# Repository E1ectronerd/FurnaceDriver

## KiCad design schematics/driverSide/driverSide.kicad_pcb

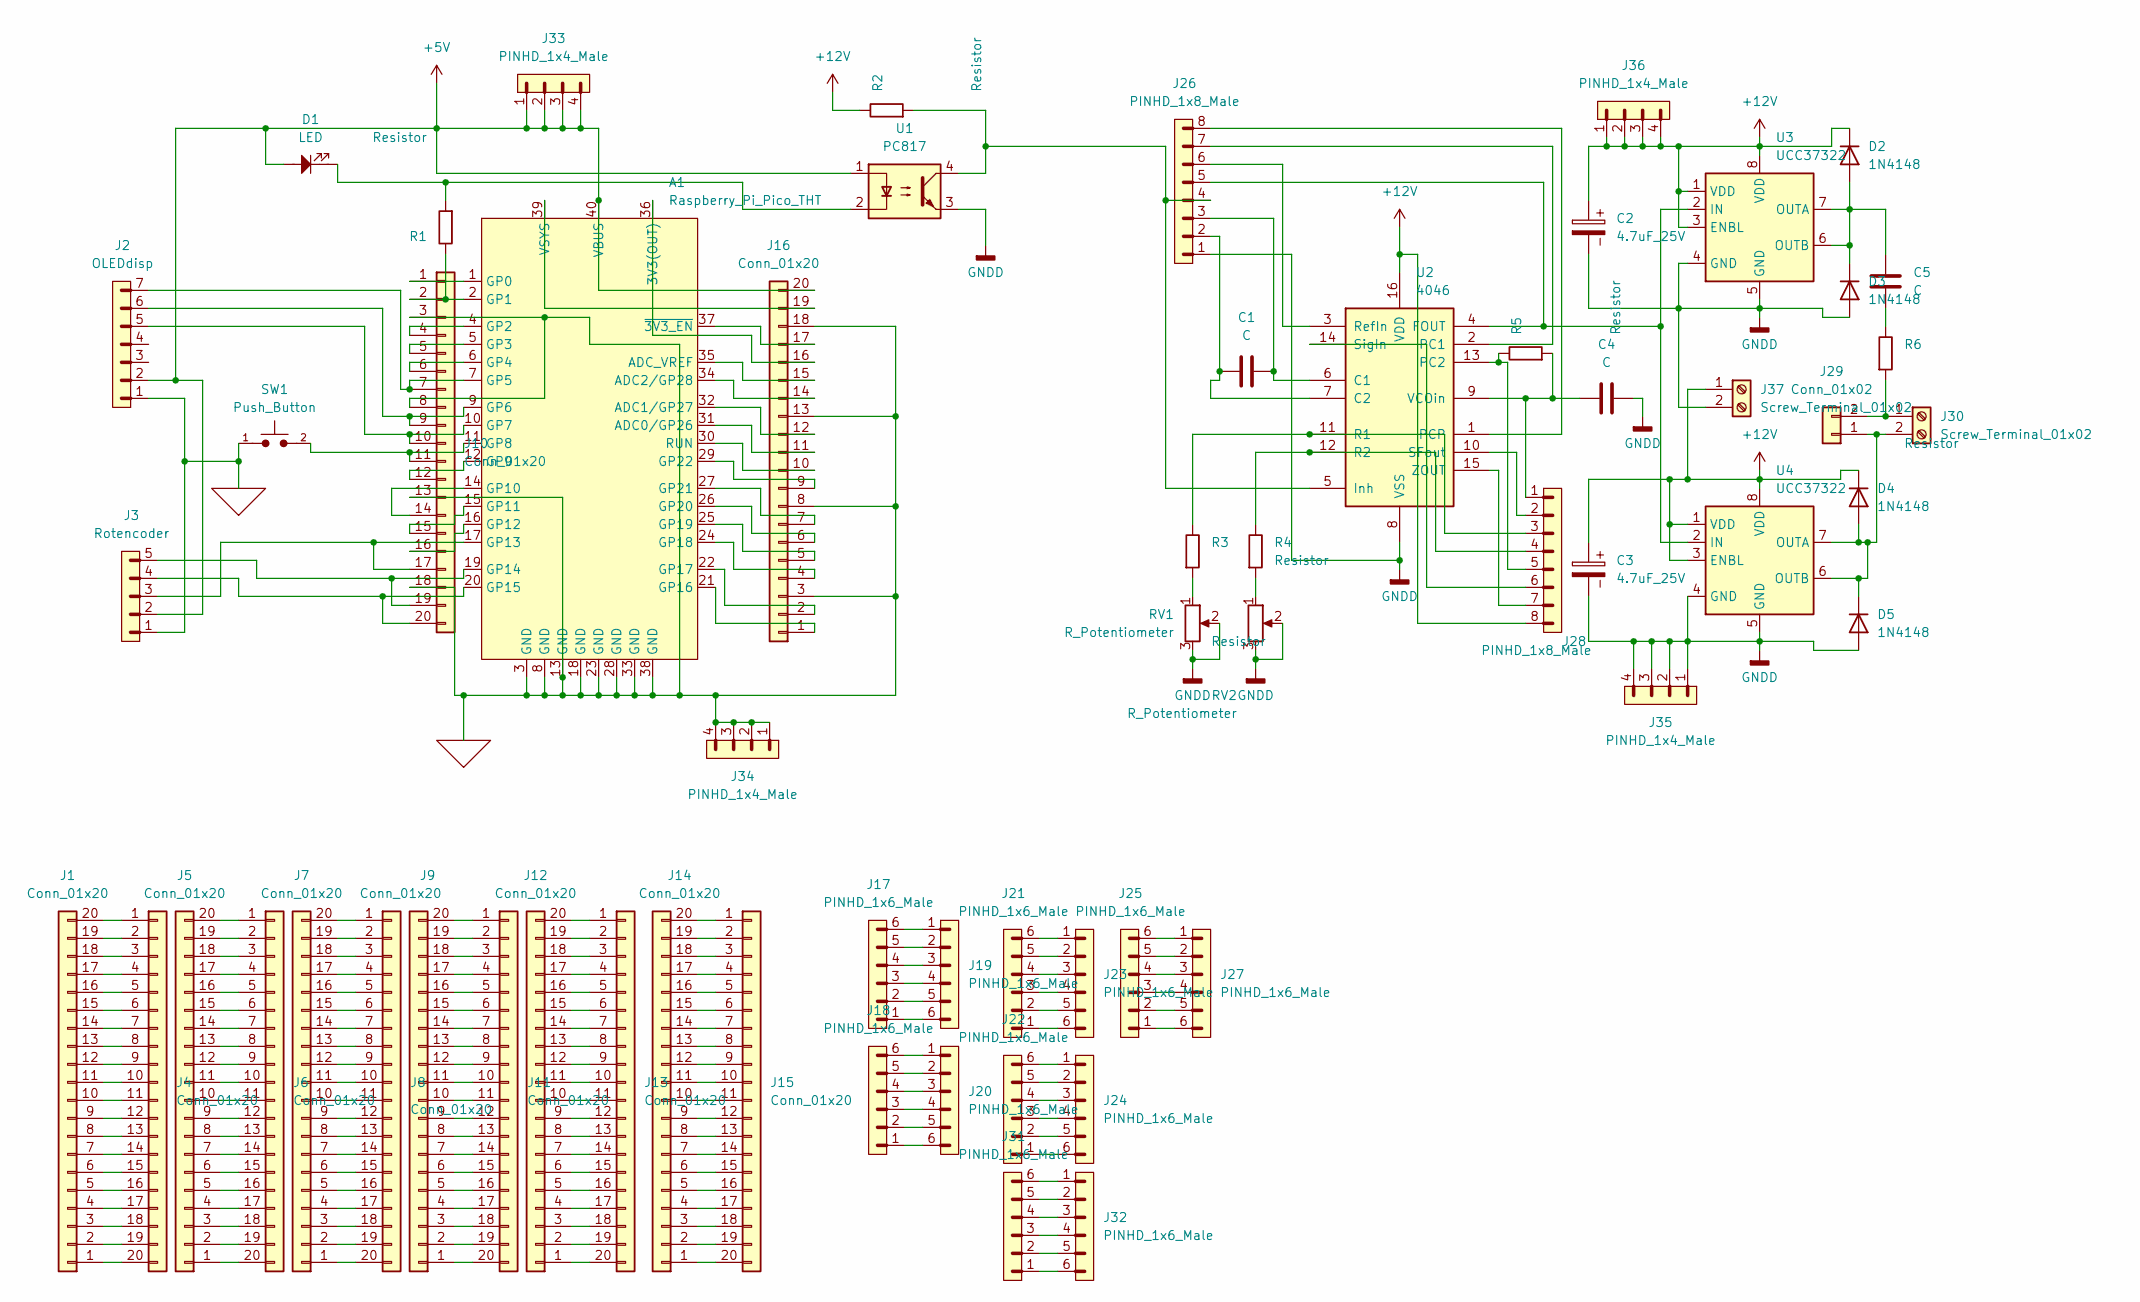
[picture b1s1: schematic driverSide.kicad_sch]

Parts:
A1: Raspberry_Pi_Pico_THT; raspberry_pi_pico_THT
C1, C4, C5: C; C_Rect_L7.0mm_W2.0mm_P5.00mm
C2, C3: 4.7uF_25V; CP_Radial_D5.0mm_P2.50mm
D1: LED; LED_D5.0mm
D2, D3, D4, D5: 1N4148; D_DO-35_SOD27_P7.62mm_Horizontal
J1, J4, J5, J6, J7, J8, J9, J10, J11, J12, J13, J14, J15, J16: Conn_01x20; PinHeader_1x20_P2.54mm_Vertical
J2: OLEDdisp; PinHeader_1x07_P2.54mm_Vertical
J3: Rotencoder; PinHeader_1x05_P2.54mm_Vertical
J17, J18, J19, J20, J21, J22, J23, J24, J25, J27, J31, J32: PINHD_1x6_Male; PinHeader_1x06_P2.54mm_Vertical
J26, J28: PINHD_1x8_Male; PinHeader_1x08_P2.54mm_Vertical
J29: Conn_01x02; TerminalBlock_Phoenix_MKDS-1,5-2-5.08_1x02_P5.08mm_Horizont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
J30, J37: Screw_Terminal_01x02; TerminalBlock_bornier-2_P5.08mm
J33, J34, J35, J36: PINHD_1x4_Male; PinHeader_1x04_P2.54mm_Vertical
R1, R2, R3, R4, R5, R6: Resistor; R_Axial_DIN0207_L6.3mm_D2.5mm_P10.16mm_Horizontal
RV1, RV2: R_Potentiometer; Potentiometer_Bourns_3266Y_Vertical
SW1: Push_Button; SW_PUSH_1P1T_6x3.5mm_H4.3_APEM_MJTP1243
U1: PC817; DIP-4_W7.62mm
U2: 4046; DIP-16_W7.62mm_LongPads
U3, U4: UCC37322; DIP-8_W7.62mm_LongPads

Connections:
+5V: A1.40 (VBUS), D1.2, J2.2, J3.2, J16.20, J33.1, J33.2, J33.3, J33.4, U1.1
+12V: C2.1, C3.1, D2.1 (K), D4.1 (K), J28.8, J36.1, J36.2, J36.3, J36.4, J37.1, R2.2, U2.16 (VDD), U3.1 (VDD), U3.3 (ENBL), U3.8 (VDD), U4.1 (VDD), U4.3 (ENBL), U4.8 (VDD)
GND: A1.3 (GND), A1.8 (GND), A1.13 (GND), A1.18 (GND), A1.23 (GND), A1.28 (GND), A1.33 (GND), A1.38 (GND), J2.1, J3.1, J10.3, J10.8, J10.13, J10.18, J16.3, J16.8, J16.13, J16.18, J34.1, J34.2, J34.3, J34.4, SW1.1
GNDD: C2.2, C3.2, C4.1, D3.2 (A), D5.2 (A), J26.1, J35.1, J35.2, J35.3, J35.4, J37.2, RV1.2, RV1.3, RV2.2, RV2.3, U1.3, U2.8 (VSS), U3.4 (GND), U3.5 (GND), U4.4 (GND), U4.5 (GND)
unnamed: A1.36 (3V3(OUT)), J16.16
unnamed: A1.31 (ADC0/GP26), J16.11
unnamed: A1.32 (ADC1/GP27), J16.12
unnamed: A1.34 (ADC2/GP28), J16.14
unnamed: A1.35 (ADC_VREF), J16.15
unnamed: A1.1 (GP0), J10.1
unnamed: A1.2 (GP1), J10.2, R1.2
unnamed: A1.4 (GP2), J10.4
unnamed: A1.5 (GP3), J10.5
unnamed: A1.6 (GP4), J10.6
unnamed: A1.7 (GP5), J2.7, J10.7
unnamed: A1.9 (GP6), J2.6, J10.9
unnamed: A1.10 (GP7), J2.5, J10.10
unnamed: A1.11 (GP8), J10.11, SW1.2
unnamed: A1.12 (GP9), J10.12
unnamed: A1.14 (GP10), J10.14
unnamed: A1.15 (GP11), J10.15
unnamed: A1.16 (GP12), J10.16
unnamed: A1.17 (GP13), J3.3, J10.17
unnamed: A1.19 (GP14), J3.5, J10.19
unnamed: A1.20 (GP15), J3.4, J10.20
unnamed: A1.21 (GP16), J16.1
unnamed: A1.22 (GP17), J16.2
unnamed: A1.24 (GP18), J16.4
unnamed: A1.25 (GP19), J16.5
unnamed: A1.26 (GP20), J16.6
unnamed: A1.27 (GP21), J16.7
unnamed: A1.29 (GP22), J16.9
unnamed: A1.30 (RUN), J16.10
unnamed: A1.39 (VSYS), J16.19
unnamed: A1.37 (~3V3_EN), J16.17
unnamed: C5.1, R6.2
unnamed: D1.1, R1.1, U1.2
unnamed: C5.2, D2.2 (A), D3.1 (K), U3.6 (OUTB), U3.7 (OUTA)
unnamed: D4.2 (A), D5.1 (K), J29.1, J30.2, U4.6 (OUTB), U4.7 (OUTA)
unnamed: J1.1, J4.20
unnamed: J1.2, J4.19
unnamed: J1.3, J4.18
unnamed: J1.4, J4.17
unnamed: J1.5, J4.16
unnamed: J1.6, J4.15
unnamed: J1.7, J4.14
unnamed: J1.8, J4.13
unnamed: J1.9, J4.12
unnamed: J1.10, J4.11
unnamed: J1.11, J4.10
unnamed: J1.12, J4.9
unnamed: J1.13, J4.8
unnamed: J1.14, J4.7
unnamed: J1.15, J4.6
unnamed: J1.16, J4.5
unnamed: J1.17, J4.4
unnamed: J1.18, J4.3
unnamed: J1.19, J4.2
unnamed: J1.20, J4.1
unnamed: J5.1, J6.20
unnamed: J5.2, J6.19
unnamed: J5.3, J6.18
unnamed: J5.4, J6.17
unnamed: J5.5, J6.16
unnamed: J5.6, J6.15
unnamed: J5.7, J6.14
unnamed: J5.8, J6.13
unnamed: J5.9, J6.12
unnamed: J5.10, J6.11
unnamed: J5.11, J6.10
unnamed: J5.12, J6.9
unnamed: J5.13, J6.8
unnamed: J5.14, J6.7
unnamed: J5.15, J6.6
unnamed: J5.16, J6.5
unnamed: J5.17, J6.4
unnamed: J5.18, J6.3
unnamed: J5.19, J6.2
unnamed: J5.20, J6.1
unnamed: J7.1, J8.20
unnamed: J7.2, J8.19
unnamed: J7.3, J8.18
unnamed: J7.4, J8.17
unnamed: J7.5, J8.16
unnamed: J7.6, J8.15
unnamed: J7.7, J8.14
unnamed: J7.8, J8.13
unnamed: J7.9, J8.12
unnamed: J7.10, J8.11
unnamed: J7.11, J8.10
unnamed: J7.12, J8.9
unnamed: J7.13, J8.8
unnamed: J7.14, J8.7
unnamed: J7.15, J8.6
unnamed: J7.16, J8.5
unnamed: J7.17, J8.4
unnamed: J7.18, J8.3
unnamed: J7.19, J8.2
unnamed: J7.20, J8.1
unnamed: J9.20, J11.1
unnamed: J9.19, J11.2
unnamed: J9.18, J11.3
unnamed: J9.17, J11.4
unnamed: J9.16, J11.5
unnamed: J9.15, J11.6
unnamed: J9.14, J11.7
unnamed: J9.13, J11.8
unnamed: J9.12, J11.9
unnamed: J9.11, J11.10
unnamed: J9.10, J11.11
unnamed: J9.9, J11.12
unnamed: J9.8, J11.13
unnamed: J9.7, J11.14
unnamed: J9.6, J11.15
unnamed: J9.5, J11.16
unnamed: J9.4, J11.17
unnamed: J9.3, J11.18
unnamed: J9.2, J11.19
unnamed: J9.1, J11.20
unnamed: J12.1, J13.20
unnamed: J12.2, J13.19
unnamed: J12.3, J13.18
unnamed: J12.4, J13.17
unnamed: J12.5, J13.16
unnamed: J12.6, J13.15
unnamed: J12.7, J13.14
unnamed: J12.8, J13.13
unnamed: J12.9, J13.12
unnamed: J12.10, J13.11
unnamed: J12.11, J13.10
unnamed: J12.12, J13.9
unnamed: J12.13, J13.8
unnamed: J12.14, J13.7
unnamed: J12.15, J13.6
unnamed: J12.16, J13.5
unnamed: J12.17, J13.4
unnamed: J12.18, J13.3
unnamed: J12.19, J13.2
unnamed: J12.20, J13.1
unnamed: J14.1, J15.20
unnamed: J14.2, J15.19
unnamed: J14.3, J15.18
unnamed: J14.4, J15.17
unnamed: J14.5, J15.16
unnamed: J14.6, J15.15
unnamed: J14.7, J15.14
unnamed: J14.8, J15.13
unnamed: J14.9, J15.12
unnamed: J14.10, J15.11
unnamed: J14.11, J15.10
unnamed: J14.12, J15.9
unnamed: J14.13, J15.8
unnamed: J14.14, J15.7
unnamed: J14.15, J15.6
unnamed: J14.16, J15.5
unnamed: J14.17, J15.4
unnamed: J14.18, J15.3
unnamed: J14.19, J15.2
unnamed: J14.20, J15.1
unnamed: J17.1, J19.6
unnamed: J17.2, J19.5
unnamed: J17.3, J19.4
unnamed: J17.4, J19.3
unnamed: J17.5, J19.2
unnamed: J17.6, J19.1
unnamed: J18.1, J20.6
unnamed: J18.2, J20.5
unnamed: J18.3, J20.4
unnamed: J18.4, J20.3
unnamed: J18.5, J20.2
unnamed: J18.6, J20.1
unnamed: J21.1, J23.6
unnamed: J21.2, J23.5
unnamed: J21.3, J23.4
unnamed: J21.4, J23.3
unnamed: J21.5, J23.2
unnamed: J21.6, J23.1
unnamed: J22.1, J24.6
unnamed: J22.2, J24.5
unnamed: J22.3, J24.4
unnamed: J22.4, J24.3
unnamed: J22.5, J24.2
unnamed: J22.6, J24.1
unnamed: J25.1, J27.6
unnamed: J25.2, J27.5
unnamed: J25.3, J27.4
unnamed: J25.4, J27.3
unnamed: J25.5, J27.2
unnamed: J25.6, J27.1
unnamed: J29.2, J30.1, R6.1
unnamed: J31.1, J32.6
unnamed: J31.2, J32.5
unnamed: J31.3, J32.4
unnamed: J31.4, J32.3
unnamed: J31.5, J32.2
unnamed: J31.6, J32.1
unnamed: R3.1, RV1.1
unnamed: R4.1, RV2.1
unnamed: C1.1, J26.3, U2.6 (C1)
unnamed: C1.2, J26.2, U2.7 (C2)
unnamed: J26.5, U2.4 (FOUT), U3.2 (IN), U4.2 (IN)
unnamed: J26.4, R2.1, U1.4, U2.5 (Inh)
unnamed: J26.7, U2.2 (PC1)
unnamed: J28.5, R5.2, U2.13 (PC2)
unnamed: J26.8, U2.1 (PCP)
unnamed: J28.3, R3.2, U2.11 (R1)
unnamed: J28.4, R4.2, U2.12 (R2)
unnamed: J26.6, U2.3 (RefIn)
unnamed: J28.2, U2.10 (SFout)
unnamed: J28.6, U2.14 (SigIn)
unnamed: C4.2, J28.1, R5.1, U2.9 (VCOin)
unnamed: J28.7, U2.15 (ZOUT)

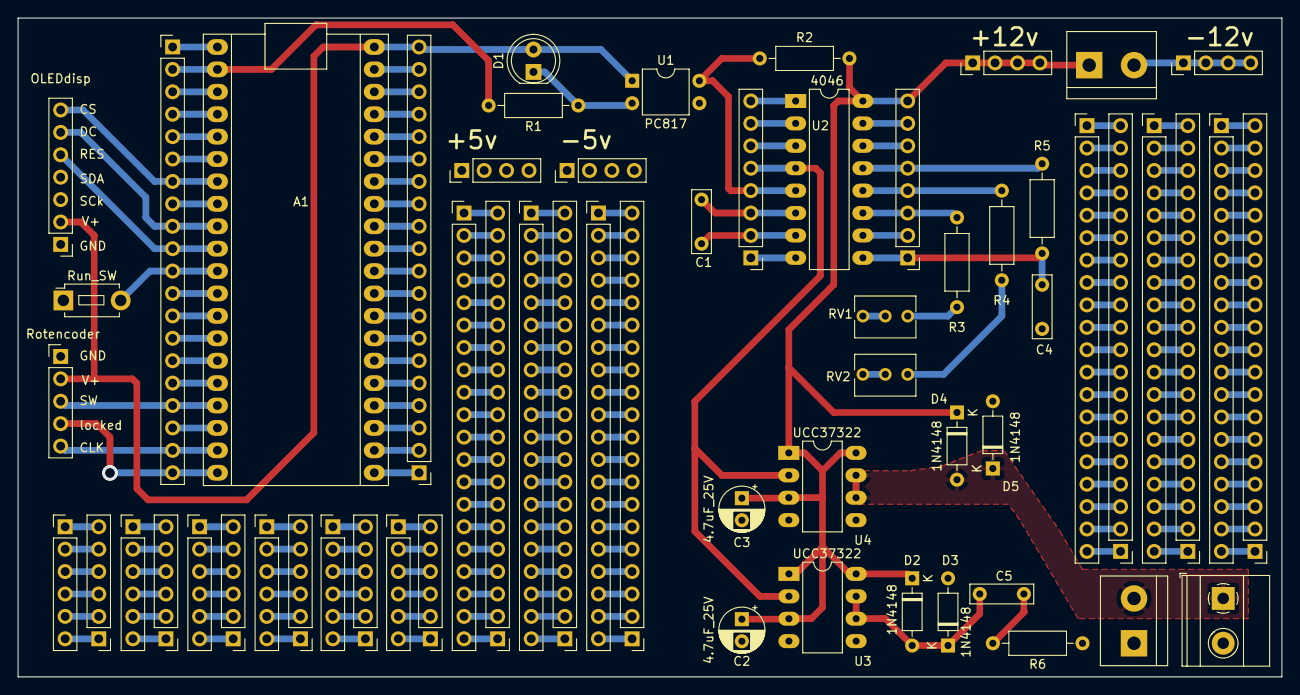
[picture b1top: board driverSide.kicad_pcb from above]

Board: 2 copper layers, 143.3 x 74.7 mm, 61 parts (0 on the bottom side), 212 nets.

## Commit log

2023-12-20 current files
2024-02-15 schematic finished
2024-02-18 first version driver board completed
